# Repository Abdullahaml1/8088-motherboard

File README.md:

# 8088-motherboard
This is the full design files for the  20x20 cm^2 8088 motheboard project.

The project aims to uplaoad a code on the flash memories of the intel 8088 micro processor  with 8051 controller. In addtion input outpu module addes to test inputs.

The motherboard consists of 5 parts:

1. The motherboard it self with the 8088 in its center. 
2. The 80851 module.
3. The input output module.
4. two memories.

# Table of Content

* [Full desing](#Full-Desing)
* [8088 Motherboard](#8088-Motherboard)
* [8051 Module](#8051-Module)
* [Input Output Module](#Input-Output-Module)
* [Memories](#Memories)

## Full Desing

## 8088 Motherboard

## 8051 Module

## Input Output Module

## Memories

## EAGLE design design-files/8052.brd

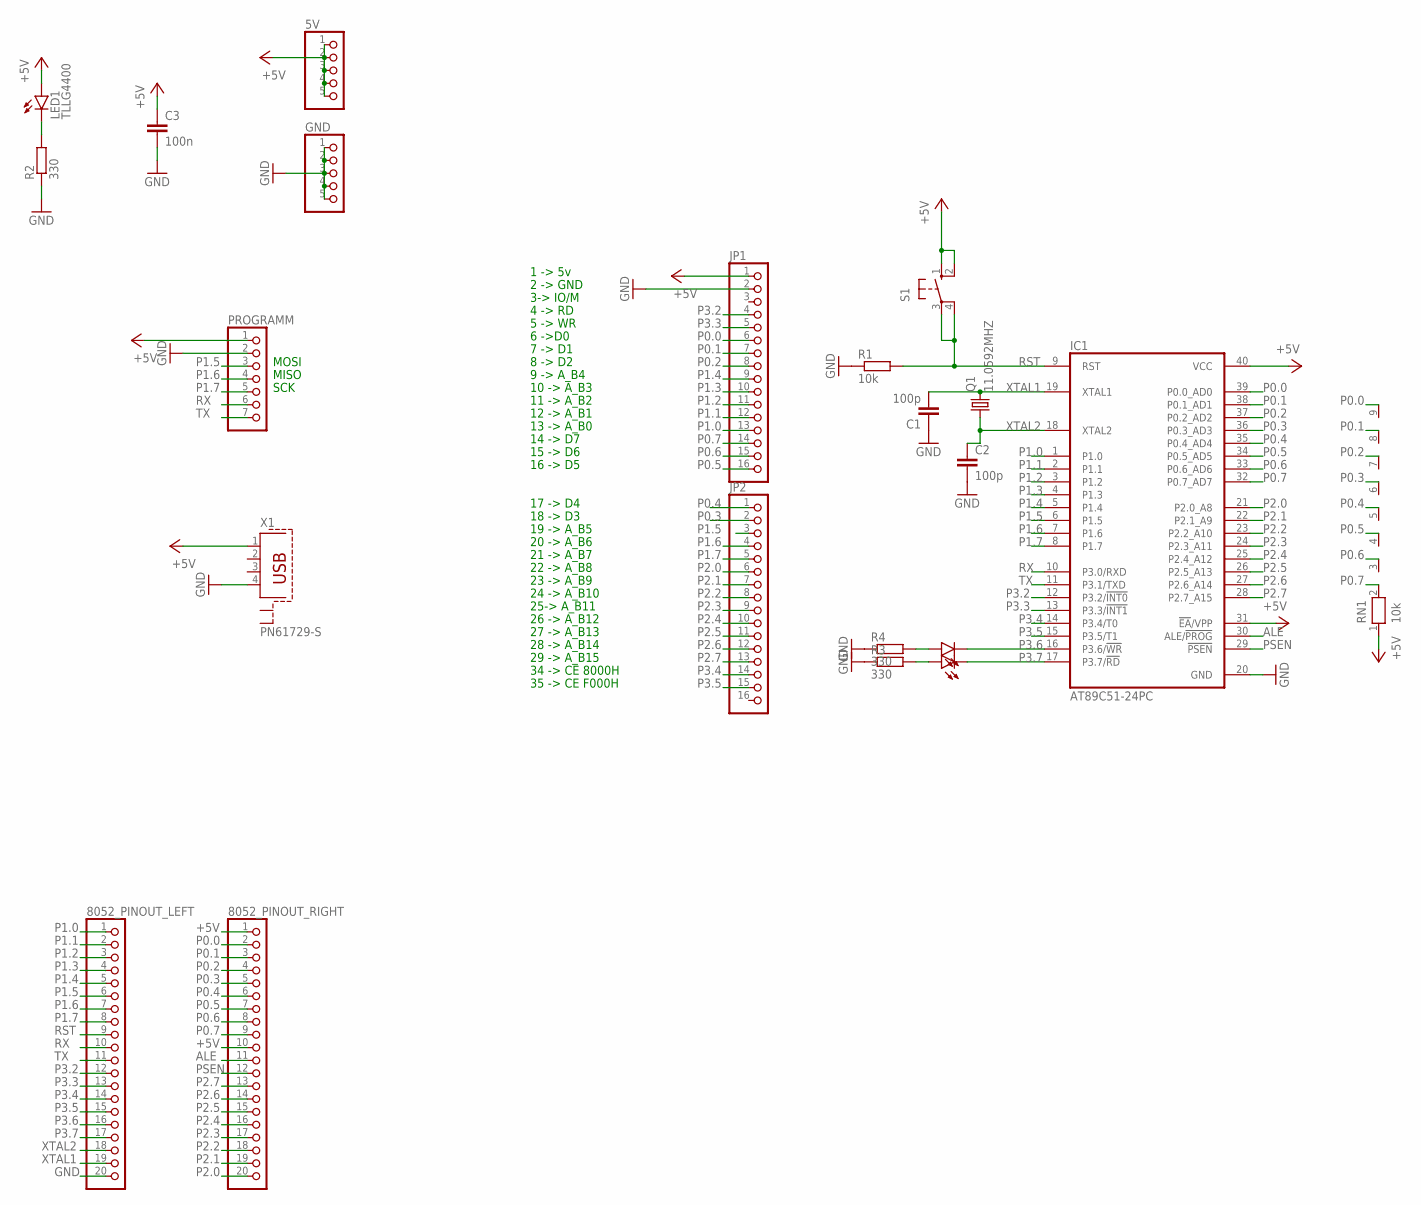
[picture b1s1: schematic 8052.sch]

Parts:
5V: PINHD-1X5; 1X05
8052_PINOUT_LEFT, 8052_PINOUT_RIGHT: PINHD-1X20; 1X20
C1, C2: 100p; C025-024X044
C3: 100n; C025-025X050
GND: PINHD-1X5; 1X05
IC1: AT89C51-24PC; DIL40
JP1, JP2: PINHD-1X16; 1X16
LED1, LED2, LED3: TLLG4400; LED3MM
PROGRAMM: PINHD-1X7/90; 1X07/90
Q1: 11.0592MHZ; HC49/S
R1: 10k; 0207/7
R2, R3, R4: 330; 0207/7
RN1: 10k; RN-9
S1: 10-XX; B3F-10XX
X1: PN61729-S

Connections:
+5V: 5V.1, 5V.2, 5V.3, 5V.4, 5V.5, 8052_PINOUT_RIGHT.1, 8052_PINOUT_RIGHT.10, C3.1, IC1.31 (!EA!/VPP), IC1.40 (VCC), JP1.1, LED1.A, PROGRAMM.1, RN1.1, S1.1 (S), S1.2 (S1), X1.1
ALE: 8052_PINOUT_RIGHT.11, IC1.30 (ALE/!PROG)
GND: 8052_PINOUT_LEFT.20, C1.1, C2.2, C3.2, GND.1, GND.2, GND.3, GND.4, GND.5, IC1.20 (GND), JP1.2, PROGRAMM.2, R1.1, R2.1, R3.1, R4.1, X1.4
unnamed: LED1.K (C), R2.2
unnamed: LED3.A, R3.2
unnamed: LED2.A, R4.2
P0.0: 8052_PINOUT_RIGHT.2, IC1.39 (P0.0_AD0), JP1.6, RN1.9
P0.1: 8052_PINOUT_RIGHT.3, IC1.38 (P0.1_AD1), JP1.7, RN1.8
P0.2: 8052_PINOUT_RIGHT.4, IC1.37 (P0.2_AD2), JP1.8, RN1.7
P0.3: 8052_PINOUT_RIGHT.5, IC1.36 (P0.3_AD3), JP2.2, RN1.6
P0.4: 8052_PINOUT_RIGHT.6, IC1.35 (P0.4_AD4), JP2.1, RN1.5
P0.5: 8052_PINOUT_RIGHT.7, IC1.34 (P0.5_AD5), JP1.16, RN1.4
P0.6: 8052_PINOUT_RIGHT.8, IC1.33 (P0.6_AD6), JP1.15, RN1.3
P0.7: 8052_PINOUT_RIGHT.9, IC1.32 (P0.7_AD7), JP1.14, RN1.2
P1.0: 8052_PINOUT_LEFT.1, IC1.1 (P1.0), JP1.13
P1.1: 8052_PINOUT_LEFT.2, IC1.2 (P1.1), JP1.12
P1.2: 8052_PINOUT_LEFT.3, IC1.3 (P1.2), JP1.11
P1.3: 8052_PINOUT_LEFT.4, IC1.4 (P1.3), JP1.10
P1.4: 8052_PINOUT_LEFT.5, IC1.5 (P1.4), JP1.9
P1.5: 8052_PINOUT_LEFT.6, IC1.6 (P1.5), JP2.3, PROGRAMM.3
P1.6: 8052_PINOUT_LEFT.7, IC1.7 (P1.6), JP2.4, PROGRAMM.4
P1.7: 8052_PINOUT_LEFT.8, IC1.8 (P1.7), JP2.5, PROGRAMM.5
P2.0: 8052_PINOUT_RIGHT.20, IC1.21 (P2.0_A8), JP2.6
P2.1: 8052_PINOUT_RIGHT.19, IC1.22 (P2.1_A9), JP2.7
P2.2: 8052_PINOUT_RIGHT.18, IC1.23 (P2.2_A10), JP2.8
P2.3: 8052_PINOUT_RIGHT.17, IC1.24 (P2.3_A11), JP2.9
P2.4: 8052_PINOUT_RIGHT.16, IC1.25 (P2.4_A12), JP2.10
P2.5: 8052_PINOUT_RIGHT.15, IC1.26 (P2.5_A13), JP2.11
P2.6: 8052_PINOUT_RIGHT.14, IC1.27 (P2.6_A14), JP2.12
P2.7: 8052_PINOUT_RIGHT.13, IC1.28 (P2.7_A15), JP2.13
P3.2: 8052_PINOUT_LEFT.12, IC1.12 (P3.2/!INT0), JP1.4
P3.3: 8052_PINOUT_LEFT.13, IC1.13 (P3.3/!INT1), JP1.5
P3.4: 8052_PINOUT_LEFT.14, IC1.14 (P3.4/T0), JP2.14
P3.5: 8052_PINOUT_LEFT.15, IC1.15 (P3.5/T1), JP2.15
P3.6: 8052_PINOUT_LEFT.16, IC1.16 (P3.6/!WR), LED2.K (C)
P3.7: 8052_PINOUT_LEFT.17, IC1.17 (P3.7/!RD), LED3.K (C)
PSEN: 8052_PINOUT_RIGHT.12, IC1.29 (!PSEN)
RST: 8052_PINOUT_LEFT.9, IC1.9 (RST), R1.2, S1.3, S1.4 (P1)
RX: 8052_PINOUT_LEFT.10, IC1.10 (P3.0/RXD), PROGRAMM.6
TX: 8052_PINOUT_LEFT.11, IC1.11 (P3.1/TXD), PROGRAMM.7
XTAL1: 8052_PINOUT_LEFT.19, C1.2, IC1.19 (XTAL1), Q1.2
XTAL2: 8052_PINOUT_LEFT.18, C2.1, IC1.18 (XTAL2), Q1.1

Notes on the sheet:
3-> IO/M
6 ->D0
13 -> A_B0
14 -> D7
21 -> A_B7
22 -> A_B8
25-> A_B11
7 -> D1
8 -> D2
9 -> A_B4
10 -> A_B3
11 -> A_B2
12 -> A_B1
15 -> D6
16 -> D5
17 -> D4
18 -> D3
19 -> A_B5
20 -> A_B6
23 -> A_B9
24 -> A_B10
26 -> A_B12
27 -> A_B13
28 -> A_B14
5 -> WR
4 -> RD
1 -> 5v
2 -> GND
29 -> A_B15
34 -> CE 8000H
35 -> CE F000H
MOSI
MISO
SCK

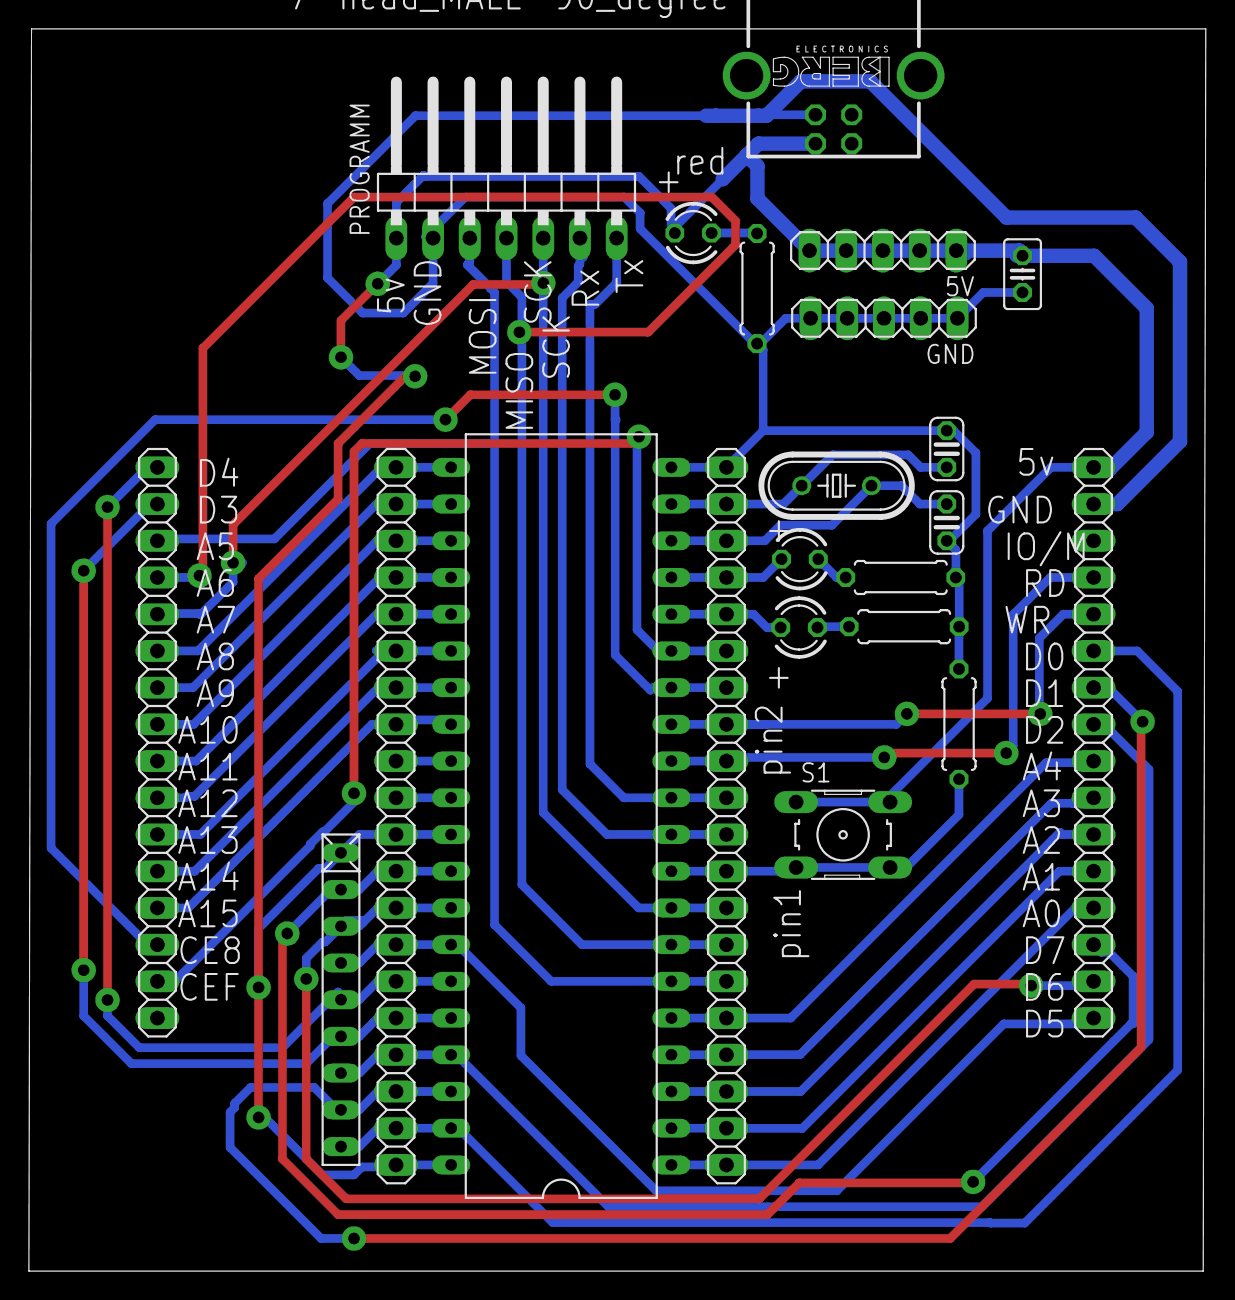
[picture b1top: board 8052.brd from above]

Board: 2 copper layers, 81.4 x 85.9 mm, 22 parts (0 on the bottom side), 42 nets.

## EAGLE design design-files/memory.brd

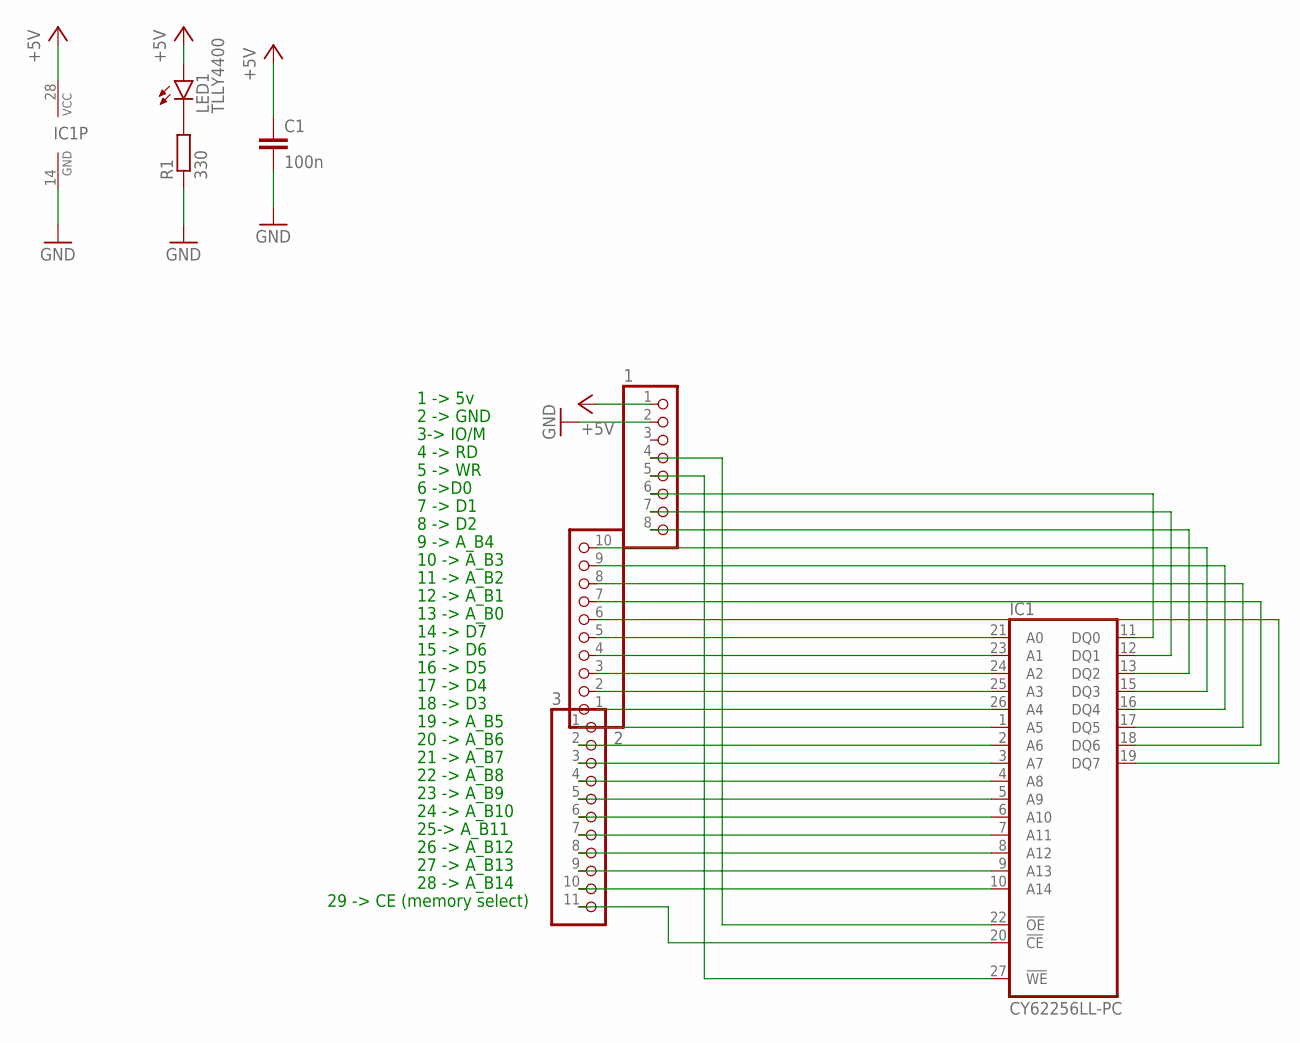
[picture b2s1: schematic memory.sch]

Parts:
1: PINHD-1X8/90; 1X08/90
2: PINHD-1X10/90; 1X10/90
3: PINHD-1X11/90; 1X11/90
C1: 100n; C025-025X050
IC1: CY62256LL-PC; DIL28-6
LED1: TLLY4400; LED3MM
R1: 330; 0207/7

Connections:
+5V: 1.1, C1.1, IC1.28 (VCC), LED1.A
GND: 1.2, C1.2, IC1.14 (GND), R1.1
unnamed: 2.5, IC1.21 (A0)
unnamed: 2.4, IC1.23 (A1)
unnamed: 2.3, IC1.24 (A2)
unnamed: 2.2, IC1.25 (A3)
unnamed: 2.1, IC1.26 (A4)
unnamed: 3.1, IC1.1 (A5)
unnamed: 3.2, IC1.2 (A6)
unnamed: 3.3, IC1.3 (A7)
unnamed: 3.4, IC1.4 (A8)
unnamed: 3.5, IC1.5 (A9)
unnamed: 3.6, IC1.6 (A10)
unnamed: 3.7, IC1.7 (A11)
unnamed: 3.8, IC1.8 (A12)
unnamed: 3.9, IC1.9 (A13)
unnamed: 3.10, IC1.10 (A14)
unnamed: 1.6, IC1.11 (DQ0)
unnamed: 1.7, IC1.12 (DQ1)
unnamed: 1.8, IC1.13 (DQ2)
unnamed: 2.10, IC1.15 (DQ3)
unnamed: 2.9, IC1.16 (DQ4)
unnamed: 2.8, IC1.17 (DQ5)
unnamed: 2.7, IC1.18 (DQ6)
unnamed: 2.6, IC1.19 (DQ7)
unnamed: LED1.K (C), R1.2
unnamed: 1.5, IC1.27 (!WE)
unnamed: 1.4, IC1.22 (!OE)
unnamed: 3.11, IC1.20 (!CE)

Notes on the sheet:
3-> IO/M
6 ->D0
13 -> A_B0
14 -> D7
21 -> A_B7
22 -> A_B8
25-> A_B11
7 -> D1
8 -> D2
9 -> A_B4
10 -> A_B3
11 -> A_B2
12 -> A_B1
15 -> D6
16 -> D5
17 -> D4
18 -> D3
19 -> A_B5
20 -> A_B6
23 -> A_B9
24 -> A_B10
26 -> A_B12
27 -> A_B13
28 -> A_B14
29 -> CE (memory select)
5 -> WR
4 -> RD
1 -> 5v
2 -> GND

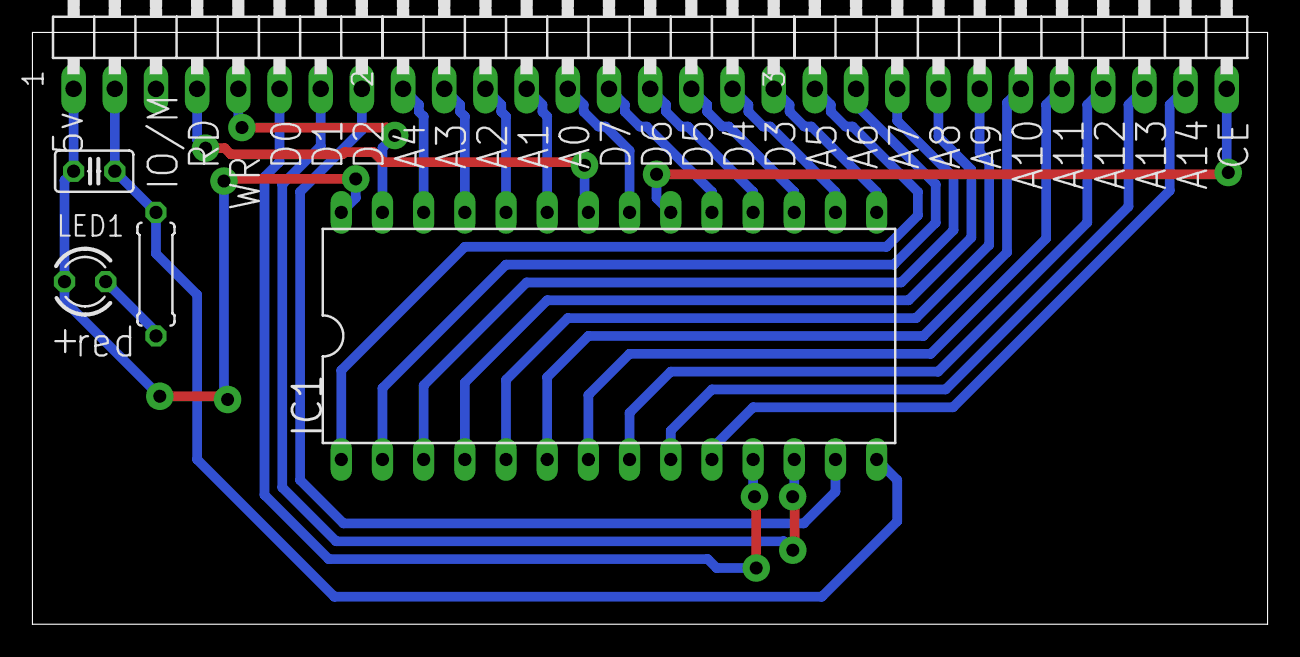
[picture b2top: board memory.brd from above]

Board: 2 copper layers, 76.2 x 36.5 mm, 7 parts (0 on the bottom side), 29 nets.

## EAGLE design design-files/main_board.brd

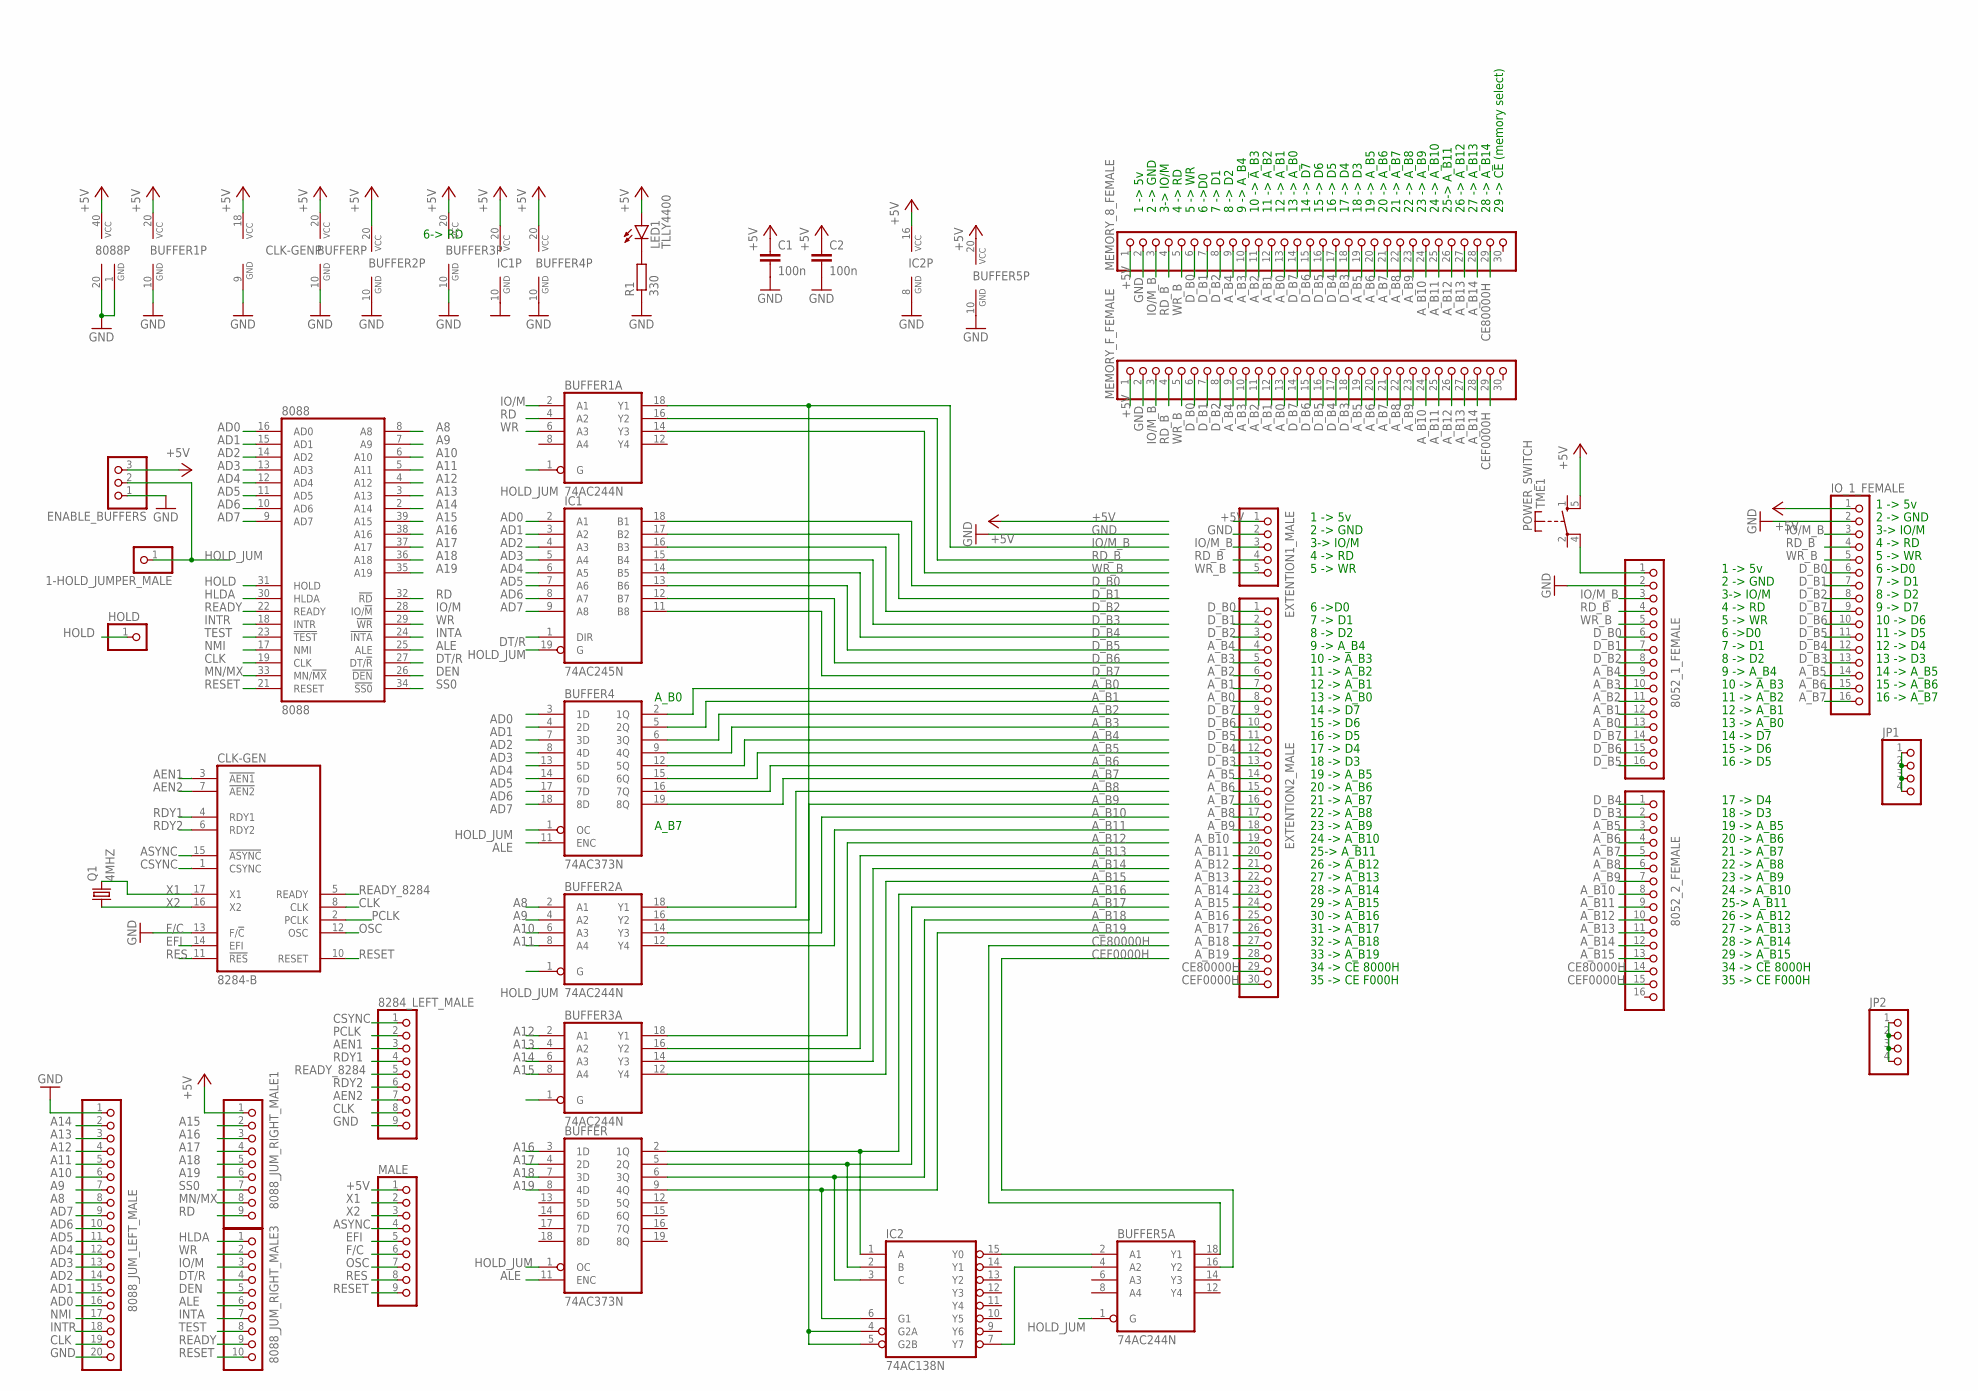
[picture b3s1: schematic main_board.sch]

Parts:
1-HOLD_JUMPER_MALE: PINHD-1X1; 1X01
8052_1_FEMALE, 8052_2_FEMALE: PINHD-1X16; 1X16
8088: 8088; DIL40
8088_JUM_LEFT_MALE: PINHD-1X20; 1X20
8088_JUM_RIGHT_MALE1, 8284_LEFT_MALE: PINHD-1X9; 1X09
8088_JUM_RIGHT_MALE3: PINHD-1X10; 1X10
BUFFER, BUFFER4: 74AC373N; DIL20
BUFFER1, BUFFER2, BUFFER3, BUFFER5: 74AC244N; DIL20
C1, C2: 100n; C025-025X050
CLK-GEN: 8284-B; DIL18
ENABLE_BUFFERS: PINHD-1X3; 1X03
EXTENTION1_MALE: PINHD-1X5; 1X05
EXTENTION2_MALE: PINHD-1X30; 1X30
HOLD: PINHD-1X1; 1X01
IC1: 74AC245N; DIL20
IC2: 74AC138N; DIL16
IO_1_FEMALE: PINHD-1X16; 1X16
JP1, JP2: PINHD-1X4; 1X04
LED1: TLLY4400; LED3MM
MALE: PINHD-1X9; 1X09
MEMORY_8_FEMALE: PINHD-1X30; 1X30
MEMORY_F_FEMALE: PINHD-1X30; 1X30
POWER_SWITCH: TME1
Q1: 4MHZ; HC49/S
R1: 330; 0204/5

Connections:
+5V: 8088.40 (VCC), 8088_JUM_RIGHT_MALE1.1, BUFFER.20 (VCC), BUFFER1.20 (VCC), BUFFER2.20 (VCC), BUFFER3.20 (VCC), BUFFER4.20 (VCC), BUFFER5.20 (VCC), C1.1, C2.1, CLK-GEN.18 (VCC), ENABLE_BUFFERS.3, EXTENTION1_MALE.1, IC1.20 (VCC), IC2.16 (VCC), IO_1_FEMALE.1, LED1.A, MALE.1, MEMORY_8_FEMALE.1, MEMORY_F_FEMALE.1, POWER_SWITCH.5 (S)
A8: 8088.8 (A8), 8088_JUM_LEFT_MALE.8, BUFFER2.2 (A1)
A9: 8088.7 (A9), 8088_JUM_LEFT_MALE.7, BUFFER2.4 (A2)
A10: 8088.6 (A10), 8088_JUM_LEFT_MALE.6, BUFFER2.6 (A3)
A11: 8088.5 (A11), 8088_JUM_LEFT_MALE.5, BUFFER2.8 (A4)
A12: 8088.4 (A12), 8088_JUM_LEFT_MALE.4, BUFFER3.2 (A1)
A13: 8088.3 (A13), 8088_JUM_LEFT_MALE.3, BUFFER3.4 (A2)
A14: 8088.2 (A14), 8088_JUM_LEFT_MALE.2, BUFFER3.6 (A3)
A15: 8088.39 (A15), 8088_JUM_RIGHT_MALE1.2, BUFFER3.8 (A4)
A16: 8088.38 (A16), 8088_JUM_RIGHT_MALE1.3, BUFFER.3 (1D)
A17: 8088.37 (A17), 8088_JUM_RIGHT_MALE1.4, BUFFER.4 (2D)
A18: 8088.36 (A18), 8088_JUM_RIGHT_MALE1.5, BUFFER.7 (3D)
A19: 8088.35 (A19), 8088_JUM_RIGHT_MALE1.6, BUFFER.8 (4D)
AD0: 8088.16 (AD0), 8088_JUM_LEFT_MALE.16, BUFFER4.3 (1D), IC1.2 (A1)
AD1: 8088.15 (AD1), 8088_JUM_LEFT_MALE.15, BUFFER4.4 (2D), IC1.3 (A2)
AD2: 8088.14 (AD2), 8088_JUM_LEFT_MALE.14, BUFFER4.7 (3D), IC1.4 (A3)
AD3: 8088.13 (AD3), 8088_JUM_LEFT_MALE.13, BUFFER4.8 (4D), IC1.5 (A4)
AD4: 8088.12 (AD4), 8088_JUM_LEFT_MALE.12, BUFFER4.13 (5D), IC1.6 (A5)
AD5: 8088.11 (AD5), 8088_JUM_LEFT_MALE.11, BUFFER4.14 (6D), IC1.7 (A6)
AD6: 8088.10 (AD6), 8088_JUM_LEFT_MALE.10, BUFFER4.17 (7D), IC1.8 (A7)
AD7: 8088.9 (AD7), 8088_JUM_LEFT_MALE.9, BUFFER4.18 (8D), IC1.9 (A8)
AEN1: 8284_LEFT_MALE.3, CLK-GEN.3 (!AEN1)
AEN2: 8284_LEFT_MALE.7, CLK-GEN.7 (!AEN2)
ALE: 8088.25 (ALE), 8088_JUM_RIGHT_MALE3.6, BUFFER.11 (ENC), BUFFER4.11 (ENC)
ASYNC: CLK-GEN.15 (!ASYNC), MALE.4
A_B0: 8052_1_FEMALE.13, BUFFER4.2 (1Q), EXTENTION2_MALE.8, MEMORY_8_FEMALE.13, MEMORY_F_FEMALE.13
A_B1: 8052_1_FEMALE.12, BUFFER4.5 (2Q), EXTENTION2_MALE.7, MEMORY_8_FEMALE.12, MEMORY_F_FEMALE.12
A_B2: 8052_1_FEMALE.11, BUFFER4.6 (3Q), EXTENTION2_MALE.6, MEMORY_8_FEMALE.11, MEMORY_F_FEMALE.11
A_B3: 8052_1_FEMALE.10, BUFFER4.9 (4Q), EXTENTION2_MALE.5, MEMORY_8_FEMALE.10, MEMORY_F_FEMALE.10
A_B4: 8052_1_FEMALE.9, BUFFER4.12 (5Q), EXTENTION2_MALE.4, MEMORY_8_FEMALE.9, MEMORY_F_FEMALE.9
A_B5: 8052_2_FEMALE.3, BUFFER4.15 (6Q), EXTENTION2_MALE.14, IO_1_FEMALE.14, MEMORY_8_FEMALE.19, MEMORY_F_FEMALE.19
A_B6: 8052_2_FEMALE.4, BUFFER4.16 (7Q), EXTENTION2_MALE.15, IO_1_FEMALE.15, MEMORY_8_FEMALE.20, MEMORY_F_FEMALE.20
A_B7: 8052_2_FEMALE.5, BUFFER4.19 (8Q), EXTENTION2_MALE.16, IO_1_FEMALE.16, MEMORY_8_FEMALE.21, MEMORY_F_FEMALE.21
A_B8: 8052_2_FEMALE.6, BUFFER2.18 (Y1), EXTENTION2_MALE.17, MEMORY_8_FEMALE.22, MEMORY_F_FEMALE.22
A_B9: 8052_2_FEMALE.7, BUFFER2.16 (Y2), EXTENTION2_MALE.18, MEMORY_8_FEMALE.23, MEMORY_F_FEMALE.23
A_B10: 8052_2_FEMALE.8, BUFFER2.14 (Y3), EXTENTION2_MALE.19, MEMORY_8_FEMALE.24, MEMORY_F_FEMALE.24
A_B11: 8052_2_FEMALE.9, BUFFER2.12 (Y4), EXTENTION2_MALE.20, MEMORY_8_FEMALE.25, MEMORY_F_FEMALE.25
A_B12: 8052_2_FEMALE.10, BUFFER3.18 (Y1), EXTENTION2_MALE.21, MEMORY_8_FEMALE.26, MEMORY_F_FEMALE.26
A_B13: 8052_2_FEMALE.11, BUFFER3.16 (Y2), EXTENTION2_MALE.22, MEMORY_8_FEMALE.27, MEMORY_F_FEMALE.27
A_B14: 8052_2_FEMALE.12, BUFFER3.14 (Y3), EXTENTION2_MALE.23, MEMORY_8_FEMALE.28, MEMORY_F_FEMALE.28
A_B15: 8052_2_FEMALE.13, BUFFER3.12 (Y4), EXTENTION2_MALE.24
A_B16: BUFFER.2 (1Q), EXTENTION2_MALE.25, IC2.1 (A)
A_B17: BUFFER.5 (2Q), EXTENTION2_MALE.26, IC2.2 (B)
A_B18: BUFFER.6 (3Q), EXTENTION2_MALE.27, IC2.3 (C)
A_B19: BUFFER.9 (4Q), EXTENTION2_MALE.28, IC2.6 (G1)
CE80000H: 8052_2_FEMALE.14, BUFFER5.18 (Y1), EXTENTION2_MALE.29, MEMORY_8_FEMALE.29
CEF0000H: 8052_2_FEMALE.15, BUFFER5.16 (Y2), EXTENTION2_MALE.30, MEMORY_F_FEMALE.29
CLK: 8088.19 (CLK), 8088_JUM_LEFT_MALE.19, 8284_LEFT_MALE.8, CLK-GEN.8 (CLK)
CSYNC: 8284_LEFT_MALE.1, CLK-GEN.1 (CSYNC)
DEN: 8088.26 (!DEN), 8088_JUM_RIGHT_MALE3.5
DT/R: 8088.27 (DT/!R), 8088_JUM_RIGHT_MALE3.4, IC1.1 (DIR)
D_B0: 8052_1_FEMALE.6, EXTENTION2_MALE.1, IC1.18 (B1), IO_1_FEMALE.6, MEMORY_8_FEMALE.6, MEMORY_F_FEMALE.6
D_B1: 8052_1_FEMALE.7, EXTENTION2_MALE.2, IC1.17 (B2), IO_1_FEMALE.7, MEMORY_8_FEMALE.7, MEMORY_F_FEMALE.7
D_B2: 8052_1_FEMALE.8, EXTENTION2_MALE.3, IC1.16 (B3), IO_1_FEMALE.8, MEMORY_8_FEMALE.8, MEMORY_F_FEMALE.8
D_B3: 8052_2_FEMALE.2, EXTENTION2_MALE.13, IC1.15 (B4), IO_1_FEMALE.13, MEMORY_8_FEMALE.18, MEMORY_F_FEMALE.18
D_B4: 8052_2_FEMALE.1, EXTENTION2_MALE.12, IC1.14 (B5), IO_1_FEMALE.12, MEMORY_8_FEMALE.17, MEMORY_F_FEMALE.17
D_B5: 8052_1_FEMALE.16, EXTENTION2_MALE.11, IC1.13 (B6), IO_1_FEMALE.11, MEMORY_8_FEMALE.16, MEMORY_F_FEMALE.16
D_B6: 8052_1_FEMALE.15, EXTENTION2_MALE.10, IC1.12 (B7), IO_1_FEMALE.10, MEMORY_8_FEMALE.15, MEMORY_F_FEMALE.15
D_B7: 8052_1_FEMALE.14, EXTENTION2_MALE.9, IC1.11 (B8), IO_1_FEMALE.9, MEMORY_8_FEMALE.14, MEMORY_F_FEMALE.14
EFI: CLK-GEN.14 (EFI), MALE.5
F/C: CLK-GEN.13 (F/!C), MALE.6
GND: 8052_1_FEMALE.2, 8088.1 (GND), 8088.20 (GND), 8088_JUM_LEFT_MALE.1, 8088_JUM_LEFT_MALE.20, 8284_LEFT_MALE.9, BUFFER.10 (GND), BUFFER1.10 (GND), BUFFER2.10 (GND), BUFFER3.10 (GND), BUFFER4.10 (GND), BUFFER5.10 (GND), C1.2, C2.2, CLK-GEN.9 (GND), ENABLE_BUFFERS.1, EXTENTION1_MALE.2, IC1.10 (GND), IC2.8 (GND), IO_1_FEMALE.2, MEMORY_8_FEMALE.2, MEMORY_F_FEMALE.2, R1.1
HLDA: 8088.30 (HLDA), 8088_JUM_RIGHT_MALE3.1
HOLD: 8088.31 (HOLD), HOLD.1
HOLD_JUM: 1-HOLD_JUMPER_MALE.1, BUFFER.1 (OC), BUFFER1.1 (G), BUFFER2.1 (G), BUFFER4.1 (OC), BUFFER5.1 (G), ENABLE_BUFFERS.2, IC1.19 (G)
INTA: 8088.24 (!INTA), 8088_JUM_RIGHT_MALE3.7
INTR: 8088.18 (INTR), 8088_JUM_LEFT_MALE.18
IO/M: 8088.28 (IO/!M), 8088_JUM_RIGHT_MALE3.3, BUFFER1.2 (A1)
IO/M_B: 8052_1_FEMALE.3, BUFFER1.18 (Y1), EXTENTION1_MALE.3, IC2.4 (G2A), IC2.5 (G2B), IO_1_FEMALE.3, MEMORY_8_FEMALE.3, MEMORY_F_FEMALE.3
MN/MX: 8088.33 (MN/!MX), 8088_JUM_RIGHT_MALE1.8
unnamed: JP1.1, JP1.2, JP1.3, JP1.4
unnamed: JP2.1, JP2.2, JP2.3, JP2.4
unnamed: LED1.K (C), R1.2
unnamed: 8052_1_FEMALE.1, POWER_SWITCH.4
unnamed: BUFFER5.2 (A1), IC2.15 (Y0)
unnamed: BUFFER5.4 (A2), IC2.7 (Y7)
NMI: 8088.17 (NMI), 8088_JUM_LEFT_MALE.17
OSC: CLK-GEN.12 (OSC), MALE.7
PCLK: 8284_LEFT_MALE.2, CLK-GEN.2 (PCLK)
RD: 8088.32 (!RD), 8088_JUM_RIGHT_MALE1.9, BUFFER1.4 (A2)
RDY1: 8284_LEFT_MALE.4, CLK-GEN.4 (RDY1)
RDY2: 8284_LEFT_MALE.6, CLK-GEN.6 (RDY2)
RD_B: 8052_1_FEMALE.4, BUFFER1.16 (Y2), EXTENTION1_MALE.4, IO_1_FEMALE.4, MEMORY_8_FEMALE.4, MEMORY_F_FEMALE.4
READY: 8088.22 (READY), 8088_JUM_RIGHT_MALE3.9
READY_8284: 8284_LEFT_MALE.5, CLK-GEN.5 (READY)
RES: CLK-GEN.11 (!RES), MALE.8
RESET: 8088.21 (RESET), 8088_JUM_RIGHT_MALE3.10, CLK-GEN.10 (RESET), MALE.9
SS0: 8088.34 (!SS0), 8088_JUM_RIGHT_MALE1.7
TEST: 8088.23 (!TEST), 8088_JUM_RIGHT_MALE3.8
WR: 8088.29 (!WR), 8088_JUM_RIGHT_MALE3.2, BUFFER1.6 (A3)
WR_B: 8052_1_FEMALE.5, BUFFER1.14 (Y3), EXTENTION1_MALE.5, IO_1_FEMALE.5, MEMORY_8_FEMALE.5, MEMORY_F_FEMALE.5
X1: CLK-GEN.17 (X1), MALE.2, Q1.2
X2: CLK-GEN.16 (X2), MALE.3, Q1.1

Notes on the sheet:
A_B0
A_B7
6-> RD
3-> IO/M
6 ->D0
13 -> A_B0
14 -> D7
21 -> A_B7
22 -> A_B8
25-> A_B11
7 -> D1
8 -> D2
9 -> A_B4
10 -> A_B3
11 -> A_B2
12 -> A_B1
15 -> D6
16 -> D5
17 -> D4
18 -> D3
19 -> A_B5
20 -> A_B6
23 -> A_B9
24 -> A_B10
26 -> A_B12
27 -> A_B13
28 -> A_B14
5 -> WR
4 -> RD
1 -> 5v
2 -> GND
29 -> A_B15
30 -> A_B16
31 -> A_B17
32 -> A_B18
33 -> A_B19
34 -> CE 8000H
35 -> CE F000H
29 -> CE (memory select)
9 -> D7

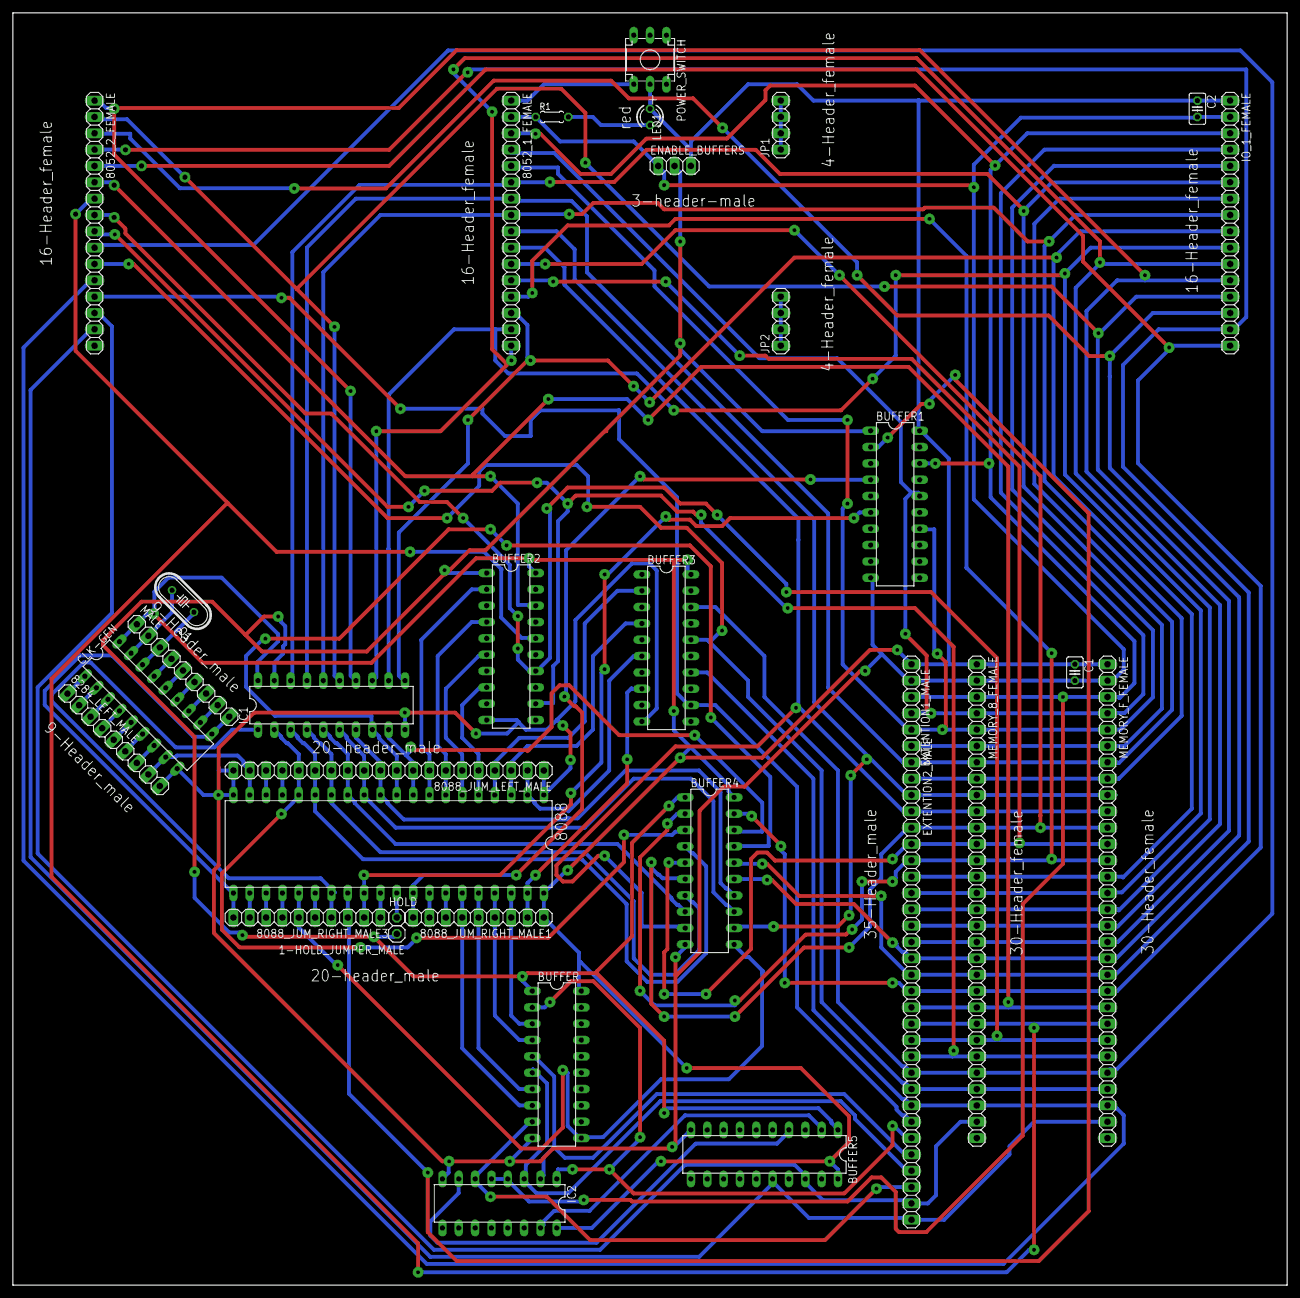
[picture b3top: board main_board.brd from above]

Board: 2 copper layers, 198.1 x 197.8 mm, 33 parts (0 on the bottom side), 93 nets.

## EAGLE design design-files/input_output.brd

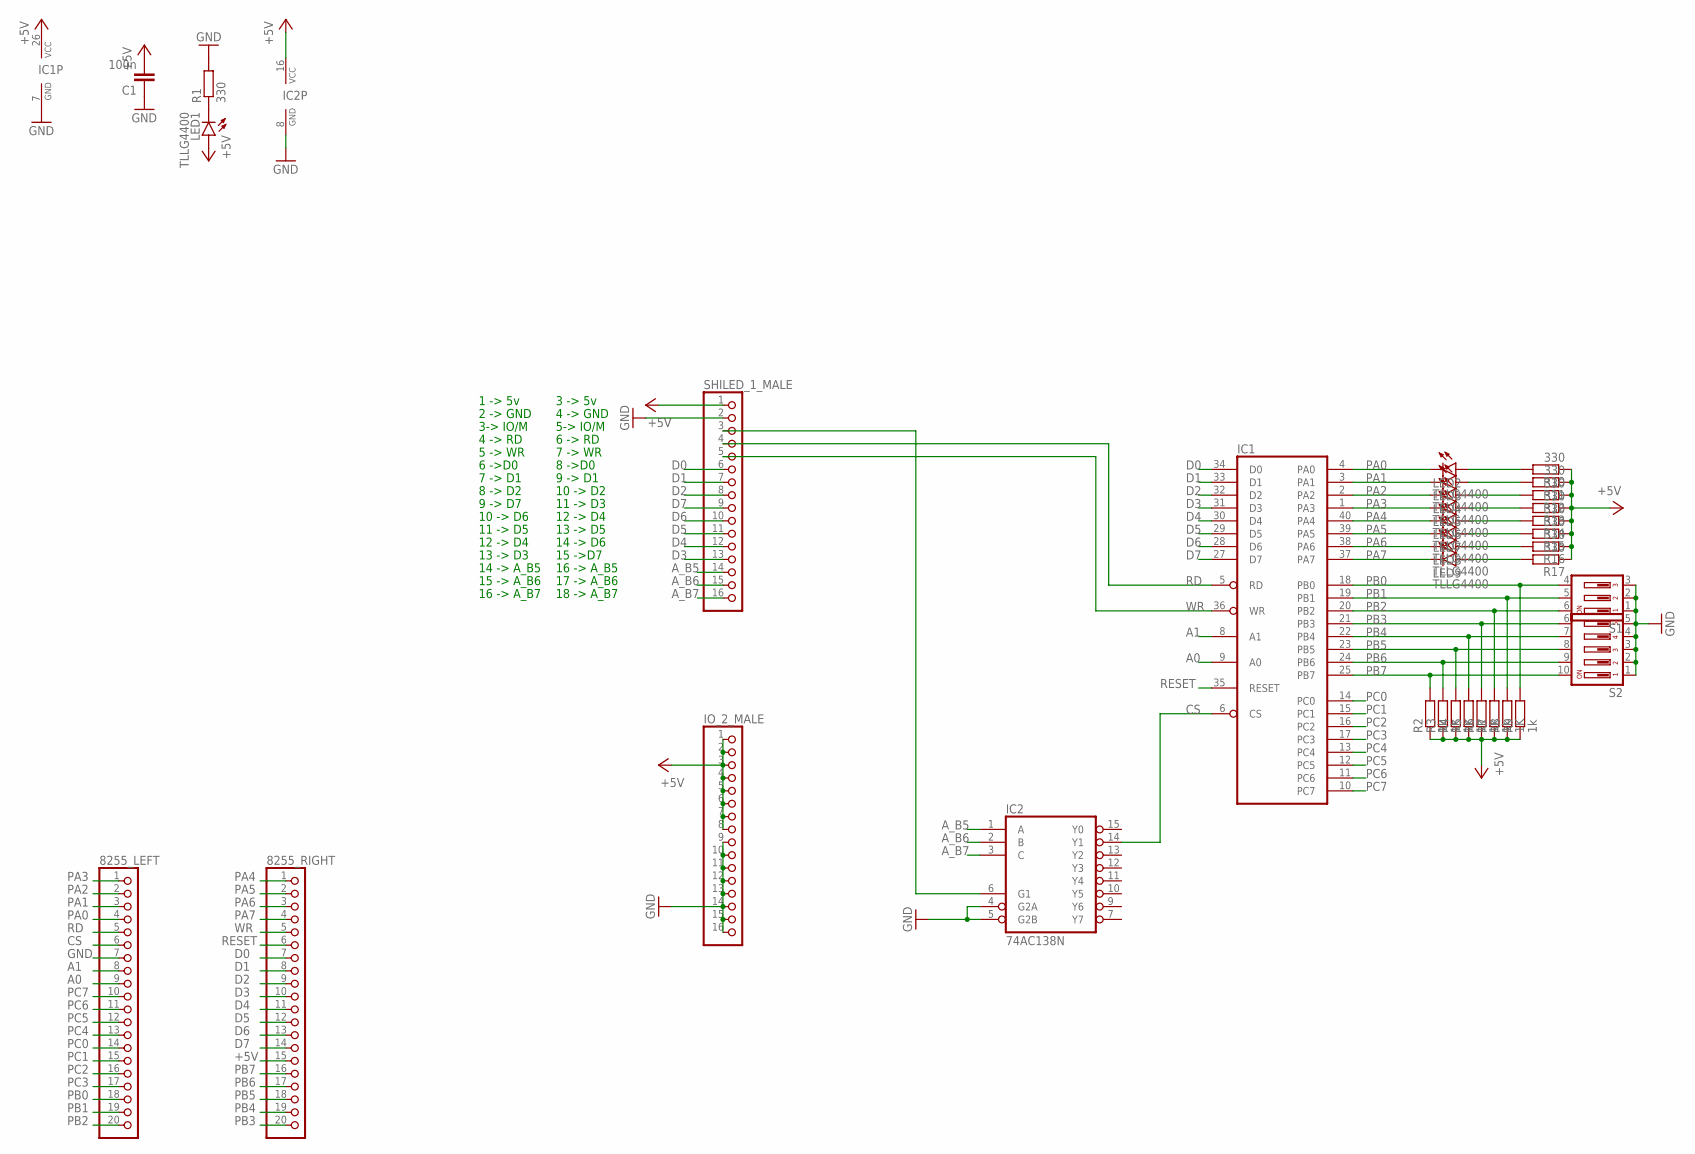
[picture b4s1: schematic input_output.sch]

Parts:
8255_LEFT, 8255_RIGHT: PINHD-1X20; 1X20
C1: 100n; C025-025X050
IC1: 8255A; DIL40
IC2: 74AC138N; DIL16
IO_2_MALE: PINHD-1X16; 1X16
LED1, LED2, LED3, LED4, LED5, LED6, LED7, LED8, LED9: TLLG4400; LED3MM
R1, R10, R11, R12, R13, R14, R15, R16, R17: 330; 0207/7
R2, R3, R4, R5, R6, R7, R9: 1k; 0207/7
R8: 1K; 0207/7
S1: DIP03YL
S2: DIP05YL
SHILED_1_MALE: PINHD-1X16; 1X16

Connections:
+5V: 8255_RIGHT.15, C1.2, IC1.26 (VCC), IC2.16 (VCC), IO_2_MALE.1, IO_2_MALE.2, IO_2_MALE.3, IO_2_MALE.4, IO_2_MALE.5, IO_2_MALE.6, IO_2_MALE.7, IO_2_MALE.8, LED1.A, R2.1, R3.1, R4.1, R5.1, R6.1, R7.1, R8.1, R9.1, R10.1, R11.1, R12.1, R13.1, R14.1, R15.1, R16.1, R17.1, SHILED_1_MALE.1
A0: 8255_LEFT.9, IC1.9 (A0)
A1: 8255_LEFT.8, IC1.8 (A1)
A_B5: IC2.1 (A), SHILED_1_MALE.14
A_B6: IC2.2 (B), SHILED_1_MALE.15
A_B7: IC2.3 (C), SHILED_1_MALE.16
CS: 8255_LEFT.6, IC1.6 (CS), IC2.14 (Y1)
D0: 8255_RIGHT.7, IC1.34 (D0), SHILED_1_MALE.6
D1: 8255_RIGHT.8, IC1.33 (D1), SHILED_1_MALE.7
D2: 8255_RIGHT.9, IC1.32 (D2), SHILED_1_MALE.8
D3: 8255_RIGHT.10, IC1.31 (D3), SHILED_1_MALE.13
D4: 8255_RIGHT.11, IC1.30 (D4), SHILED_1_MALE.12
D5: 8255_RIGHT.12, IC1.29 (D5), SHILED_1_MALE.11
D6: 8255_RIGHT.13, IC1.28 (D6), SHILED_1_MALE.10
D7: 8255_RIGHT.14, IC1.27 (D7), SHILED_1_MALE.9
GND: 8255_LEFT.7, C1.1, IC1.7 (GND), IC2.4 (G2A), IC2.5 (G2B), IC2.8 (GND), IO_2_MALE.9, IO_2_MALE.10, IO_2_MALE.11, IO_2_MALE.12, IO_2_MALE.13, IO_2_MALE.14, IO_2_MALE.15, IO_2_MALE.16, R1.2, S1.1, S1.2, S1.3, S2.1, S2.2, S2.3, S2.4, S2.5, SHILED_1_MALE.2
unnamed: LED1.K (C), R1.1
unnamed: LED2.A, R10.2
unnamed: LED3.A, R11.2
unnamed: LED4.A, R12.2
unnamed: LED5.A, R13.2
unnamed: LED6.A, R14.2
unnamed: LED7.A, R15.2
unnamed: LED8.A, R16.2
unnamed: LED9.A, R17.2
unnamed: IC2.6 (G1), SHILED_1_MALE.3
PA0: 8255_LEFT.4, IC1.4 (PA0), LED2.K (C)
PA1: 8255_LEFT.3, IC1.3 (PA1), LED3.K (C)
PA2: 8255_LEFT.2, IC1.2 (PA2), LED4.K (C)
PA3: 8255_LEFT.1, IC1.1 (PA3), LED5.K (C)
PA4: 8255_RIGHT.1, IC1.40 (PA4), LED6.K (C)
PA5: 8255_RIGHT.2, IC1.39 (PA5), LED7.K (C)
PA6: 8255_RIGHT.3, IC1.38 (PA6), LED8.K (C)
PA7: 8255_RIGHT.4, IC1.37 (PA7), LED9.K (C)
PB0: 8255_LEFT.18, IC1.18 (PB0), R9.2, S1.4
PB1: 8255_LEFT.19, IC1.19 (PB1), R8.2, S1.5
PB2: 8255_LEFT.20, IC1.20 (PB2), R7.2, S1.6
PB3: 8255_RIGHT.20, IC1.21 (PB3), R6.2, S2.6
PB4: 8255_RIGHT.19, IC1.22 (PB4), R5.2, S2.7
PB5: 8255_RIGHT.18, IC1.23 (PB5), R4.2, S2.8
PB6: 8255_RIGHT.17, IC1.24 (PB6), R3.2, S2.9
PB7: 8255_RIGHT.16, IC1.25 (PB7), R2.2, S2.10
PC0: 8255_LEFT.14, IC1.14 (PC0)
PC1: 8255_LEFT.15, IC1.15 (PC1)
PC2: 8255_LEFT.16, IC1.16 (PC2)
PC3: 8255_LEFT.17, IC1.17 (PC3)
PC4: 8255_LEFT.13, IC1.13 (PC4)
PC5: 8255_LEFT.12, IC1.12 (PC5)
PC6: 8255_LEFT.11, IC1.11 (PC6)
PC7: 8255_LEFT.10, IC1.10 (PC7)
RD: 8255_LEFT.5, IC1.5 (RD), SHILED_1_MALE.4
RESET: 8255_RIGHT.6, IC1.35 (RESET)
WR: 8255_RIGHT.5, IC1.36 (WR), SHILED_1_MALE.5

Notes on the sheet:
5-> IO/M
8 ->D0
15 ->D7
9 -> D1
10 -> D2
11 -> D3
12 -> D4
13 -> D5
14 -> D6
7 -> WR
6 -> RD
3 -> 5v
4 -> GND
16 -> A_B5
17 -> A_B6
18 -> A_B7
3-> IO/M
6 ->D0
7 -> D1
8 -> D2
5 -> WR
4 -> RD
1 -> 5v
2 -> GND
9 -> D7
16 -> A_B7
10 -> D6
11 -> D5
13 -> D3
14 -> A_B5
15 -> A_B6
